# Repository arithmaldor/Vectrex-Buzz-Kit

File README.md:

# Copyright and Disclaimer
Copyright: Jacob Proctor 2018

This documentation describes Open Hardware and is licensed under the
CERN OHL v. 1.2.

You may redistribute and modify this documentation under the terms of the
CERN OHL v.1.2. (http://ohwr.org/cernohl). This documentation is distributed
WITHOUT ANY EXPRESS OR IMPLIED WARRANTY, INCLUDING OF
MERCHANTABILITY, SATISFACTORY QUALITY AND FITNESS FOR A
PARTICULAR PURPOSE. Please see the CERN OHL v.1.2 for applicable
conditions

# Buzz Fix Kit
Use this board to make assembly of the buzz fix kit a bit easier. I have included an SMD version as well as a THT version. The THT version can be used with the
kit sold on Console5.com here:https://console5.com/store/vectrex-de-buzz-kit.html

See https://console5.com/wiki/Vectrex_PreAmp_Buzz_Reduction for more informationa about the circuit.

Credit to Console5.com and Bill Seiler for the schematic

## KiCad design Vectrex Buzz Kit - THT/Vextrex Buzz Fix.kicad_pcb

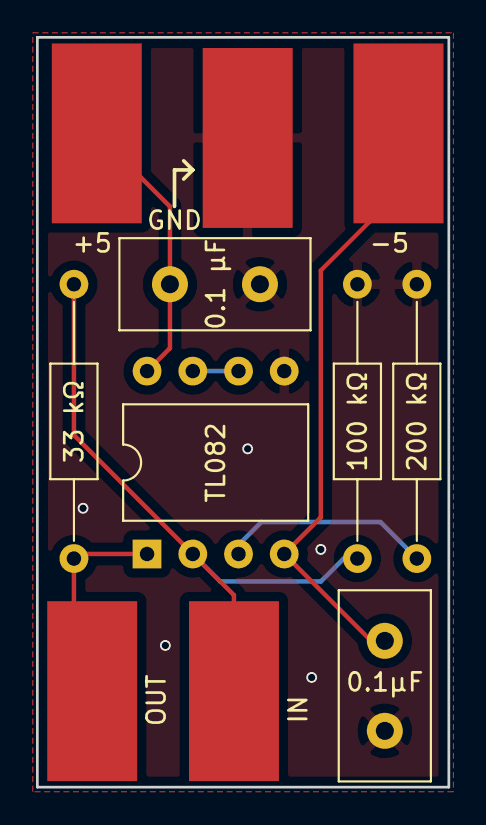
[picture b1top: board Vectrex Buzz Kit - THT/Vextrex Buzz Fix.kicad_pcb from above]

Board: 2 copper layers, 22.9 x 41.7 mm, 11 parts (0 on the bottom side), 6 nets.

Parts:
0.1 μF, 0.1μF: 0.1uF; C_Disc_D10.5mm_W5.0mm_P5.00mm
33 kΩ: 33K; R_Axial_DIN0207_L6.3mm_D2.5mm_P15.24mm_Horizontal
100 kΩ: 100K; R_Axial_DIN0207_L6.3mm_D2.5mm_P15.24mm_Horizontal
200 kΩ: 200K; R_Axial_DIN0207_L6.3mm_D2.5mm_P15.24mm_Horizontal
+5: +5V; SolderWirePad_single_SMD_5x10mm
-5: -5V; SolderWirePad_single_SMD_5x10mm
GND: GND; SolderWirePad_single_SMD_5x10mm
IN: IN; SolderWirePad_single_SMD_5x10mm
OUT: OUT; SolderWirePad_single_SMD_5x10mm
TL082: TL082; DIP-8_W10.16mm

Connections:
+5V: 0.1 μF.1, +5.1, TL082.8
-5V: 0.1μF.1, -5.1, TL082.4
GND: 0.1 μF.2, 0.1μF.2, 100 kΩ.2, 200 kΩ.2, GND.1, TL082.5
INPUT: 33 kΩ.2, 100 kΩ.1, IN.1, TL082.2
unnamed: 200 kΩ.1, TL082.3
OUTPUT: 33 kΩ.1, OUT.1, TL082.1

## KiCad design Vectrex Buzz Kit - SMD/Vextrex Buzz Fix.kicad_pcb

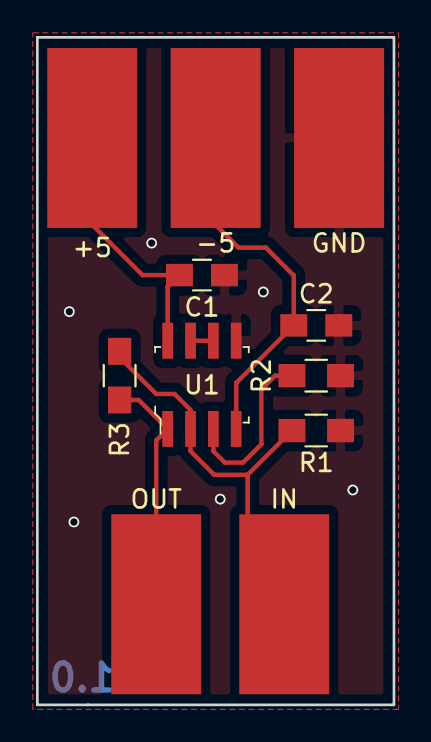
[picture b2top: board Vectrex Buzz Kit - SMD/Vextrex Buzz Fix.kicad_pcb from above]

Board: 2 copper layers, 19.8 x 37.1 mm, 11 parts (0 on the bottom side), 6 nets.

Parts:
+5: +5V; SolderWirePad_single_SMD_5x10mm
-5: -5V; SolderWirePad_single_SMD_5x10mm
C1, C2: 0.1uF; C_0805_HandSoldering
GND: GND; SolderWirePad_single_SMD_5x10mm
IN: IN; SolderWirePad_single_SMD_5x10mm
OUT: OUT; SolderWirePad_single_SMD_5x10mm
R1: 100K; R_0805_HandSoldering
R2: 200K; R_0805_HandSoldering
R3: 33K; R_0805_HandSoldering
U1: TL082; SOIC-8_W3.9mm

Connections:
+5V: +5.1, C1.1, U1.8
-5V: -5.1, C2.1, U1.4
GND: C1.2, C2.2, GND.1, R1.2, R2.2, U1.5
INPUT: IN.1, R1.1, R3.2, U1.2
unnamed: R2.1, U1.3
OUTPUT: OUT.1, R3.1, U1.1

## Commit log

2018-06-03 Version 1.0
2018-06-30 1.1
    added a tiny but of solder mask keepout in an attempt to make this board look right for jlcpcb
2018-06-30 GERBERS
2018-06-30 jlcpcb
2020-06-08 Fixed Unintentional Antenna
    Thanks to mobiusstriptech for the fix, applied to both SMD and THT versions.
2020-06-08 Changed gerber file names
